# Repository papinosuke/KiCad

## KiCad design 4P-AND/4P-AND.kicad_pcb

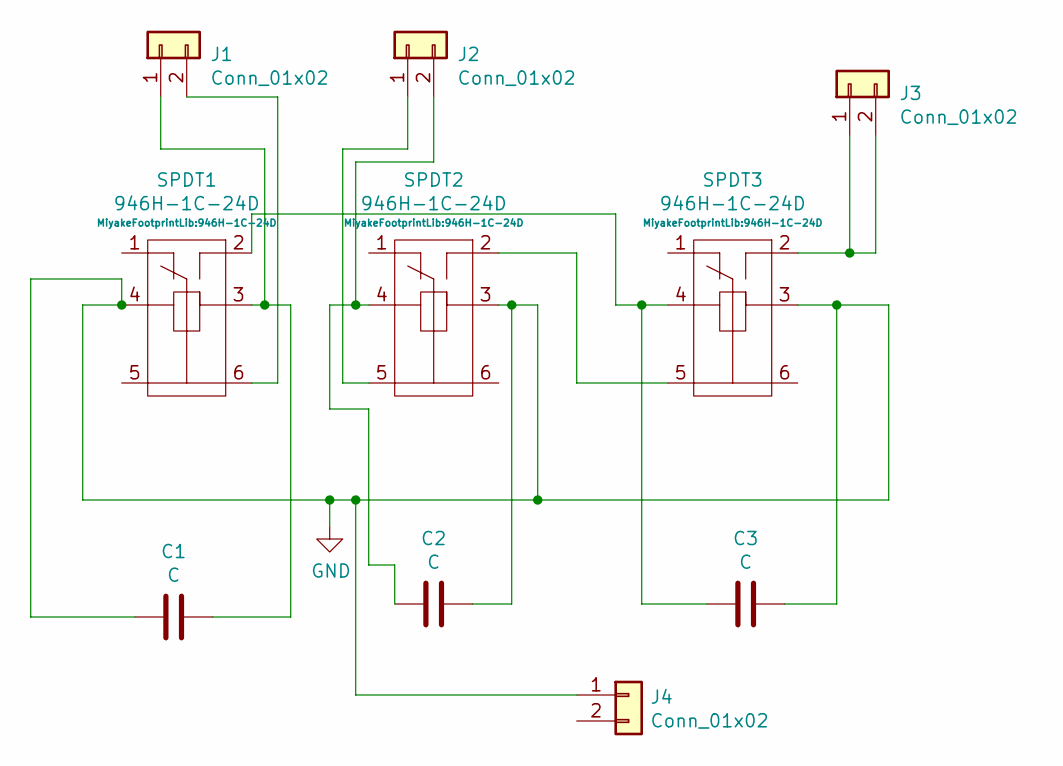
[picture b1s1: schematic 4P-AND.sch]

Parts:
C1, C2, C3: C; Condensor
J1, J2, J3, J4: Conn_01x02; PinHeader_1x02_P2.54mm_Vertical
SPDT1, SPDT2, SPDT3: 946H-1C-24D

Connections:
GND: C1.2, C2.1, C3.1, J4.1, SPDT1.4, SPDT2.3, SPDT3.3
unnamed: C1.1, J1.1, SPDT1.3
unnamed: C2.2, J2.2, SPDT2.4
unnamed: C3.2, SPDT1.2, SPDT3.4
unnamed: J1.2, SPDT1.6
unnamed: J2.1, SPDT2.5
unnamed: J3.1, J3.2, SPDT3.2
unnamed: SPDT2.2, SPDT3.5

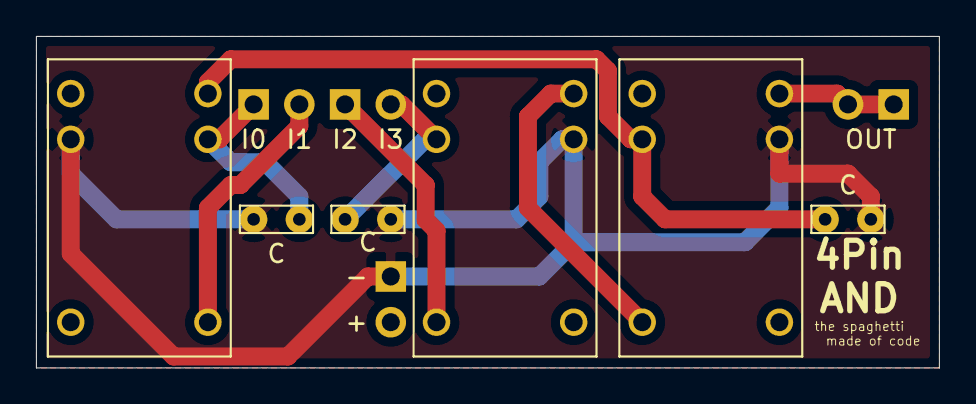
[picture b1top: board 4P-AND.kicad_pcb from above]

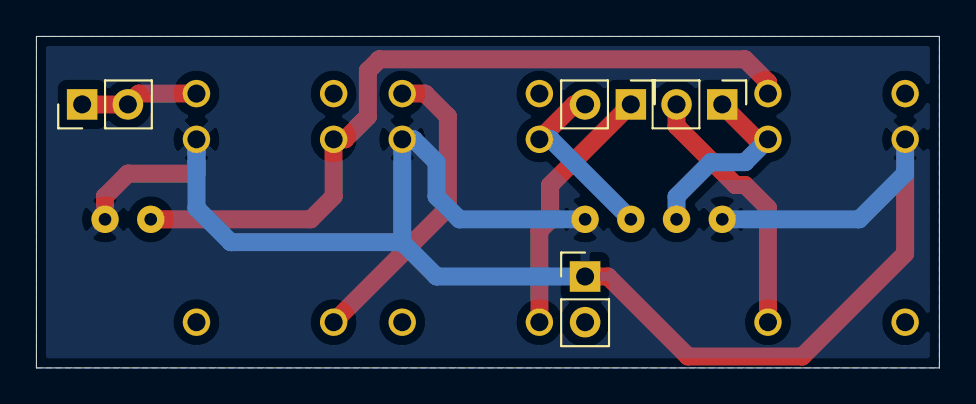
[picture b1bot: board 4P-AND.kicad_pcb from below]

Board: 2 copper layers, 50.2 x 18.4 mm, 10 parts (4 on the bottom side), 8 nets.

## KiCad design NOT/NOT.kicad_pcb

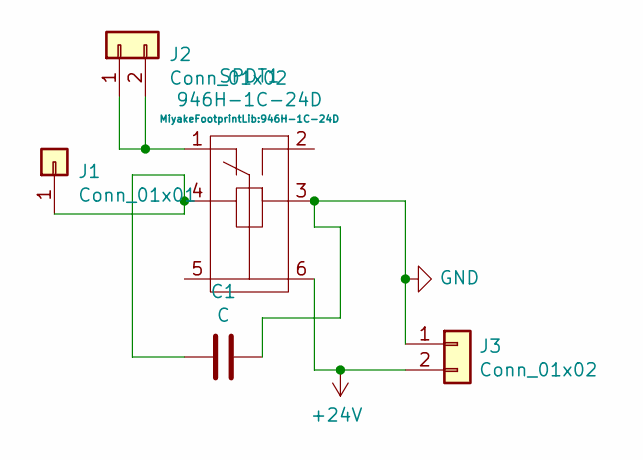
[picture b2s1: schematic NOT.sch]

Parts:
C1: C; Condensor
J1: Conn_01x01; PinHeader_1x01_P2.54mm_Vertical
J2, J3: Conn_01x02; PinHeader_1x02_P2.54mm_Vertical
SPDT1: 946H-1C-24D

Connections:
+24V: J3.2, SPDT1.6
GND: C1.1, J3.1, SPDT1.3
unnamed: C1.2, J1.1, SPDT1.4
unnamed: J2.1, J2.2, SPDT1.1

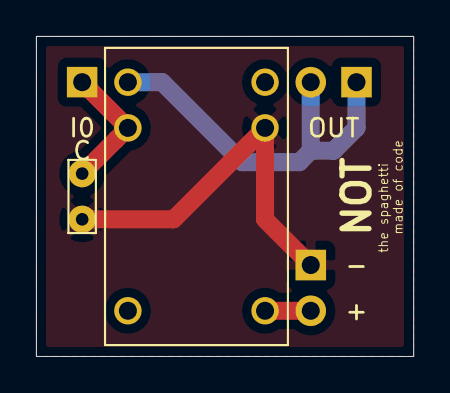
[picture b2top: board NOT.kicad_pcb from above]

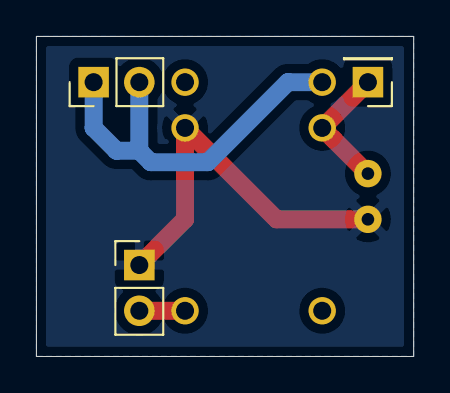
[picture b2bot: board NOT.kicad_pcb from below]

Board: 2 copper layers, 21.0 x 17.8 mm, 5 parts (3 on the bottom side), 4 nets.

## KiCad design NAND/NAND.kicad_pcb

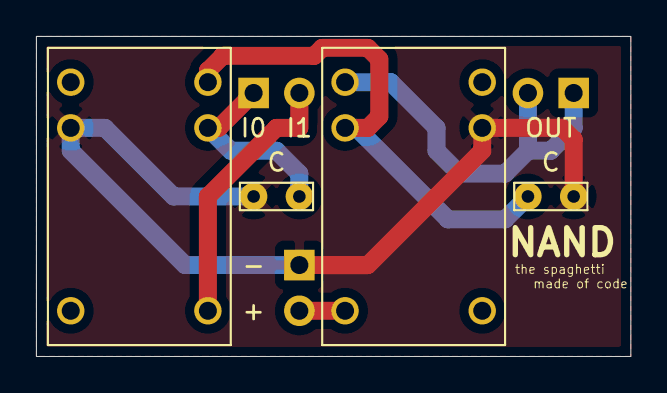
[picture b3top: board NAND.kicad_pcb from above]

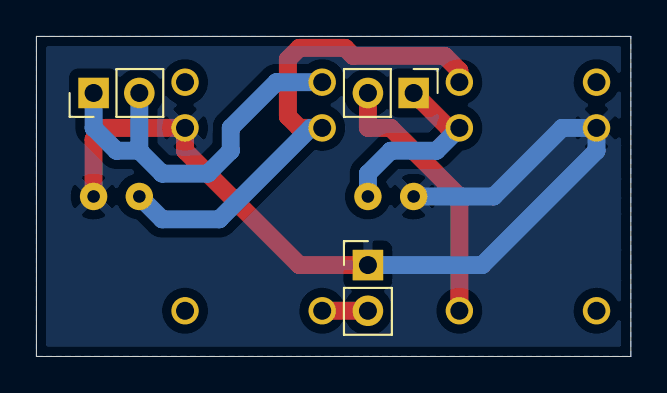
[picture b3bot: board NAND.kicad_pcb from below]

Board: 2 copper layers, 33.0 x 17.8 mm, 7 parts (3 on the bottom side), 6 nets.

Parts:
C1, C2: C; Condensor
J1, J2, J3: Conn_01x02; PinHeader_1x02_P2.54mm_Vertical
SPDT1, SPDT2: 946H-1C-24D

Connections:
+24V: J2.2, SPDT2.5
GND: C1.2, C2.1, J2.1, SPDT1.4, SPDT2.3
unnamed: C1.1, J1.1, SPDT1.3
unnamed: C2.2, SPDT1.2, SPDT2.4
unnamed: J1.2, SPDT1.6
unnamed: J3.1, J3.2, SPDT2.1

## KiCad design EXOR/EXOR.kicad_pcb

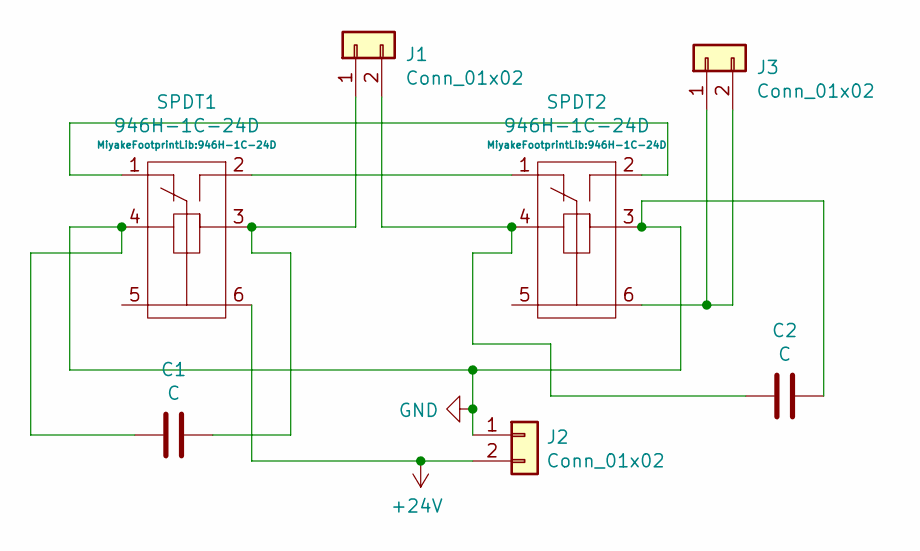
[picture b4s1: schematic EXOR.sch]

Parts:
C1, C2: C; Condensor
J1, J2, J3: Conn_01x02; PinHeader_1x02_P2.54mm_Vertical
SPDT1, SPDT2: 946H-1C-24D

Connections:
+24V: J2.2, SPDT1.6
GND: C1.2, C2.1, J2.1, SPDT1.4, SPDT2.3
unnamed: C1.1, J1.1, SPDT1.3
unnamed: C2.2, J1.2, SPDT2.4
unnamed: J3.1, J3.2, SPDT2.6
unnamed: SPDT1.1, SPDT2.2
unnamed: SPDT1.2, SPDT2.1

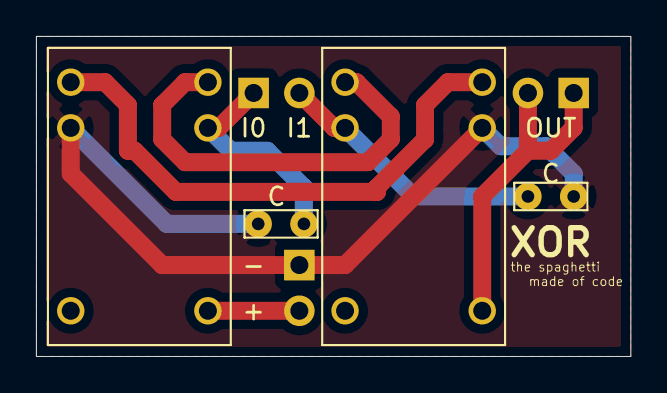
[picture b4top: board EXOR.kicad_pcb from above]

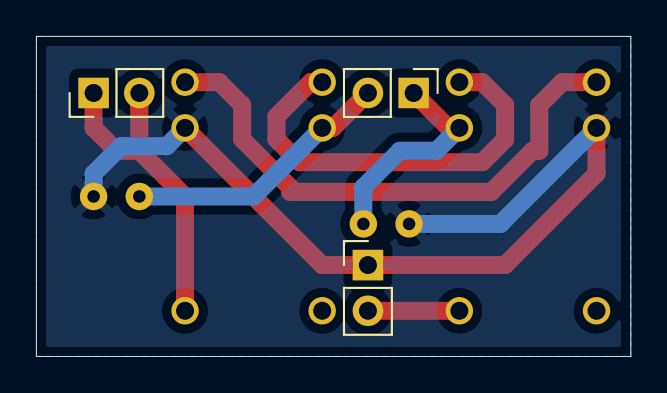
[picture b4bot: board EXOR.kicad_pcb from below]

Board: 2 copper layers, 33.0 x 17.8 mm, 7 parts (3 on the bottom side), 7 nets.
